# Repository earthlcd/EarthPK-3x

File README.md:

# EarthPK-3x Pico Pi Breakout Board for the 3x PCB

These are the design file for the EarthPK-3x Pico Pi Breakout Board that can be used with EarthLCD ezLCD-3x smart LCD's such asthe 3.5" ezLCD-303 and the ezLCD-304. Also this board with the mating DF-11 connector and the bare PCB along with a a bundled 4.3" ezLCD-3x is below: 

[ezLCD-3043-PK](https://earthlcd.com/products/ezlcd-3043-pk)

The arduino library to use the arduino IDE with this is below:

[arLCD Library](https://github.com/earthlcd/arLCDLib)

Schematic:
[REV-X2](https://github.com/earthlcd/EarthPK-3x/blob/master/schematics/ezLCD-303-PicoPi-Breakout-Board-REV-X2.pdf)

QuickStart Guide (coming soon)

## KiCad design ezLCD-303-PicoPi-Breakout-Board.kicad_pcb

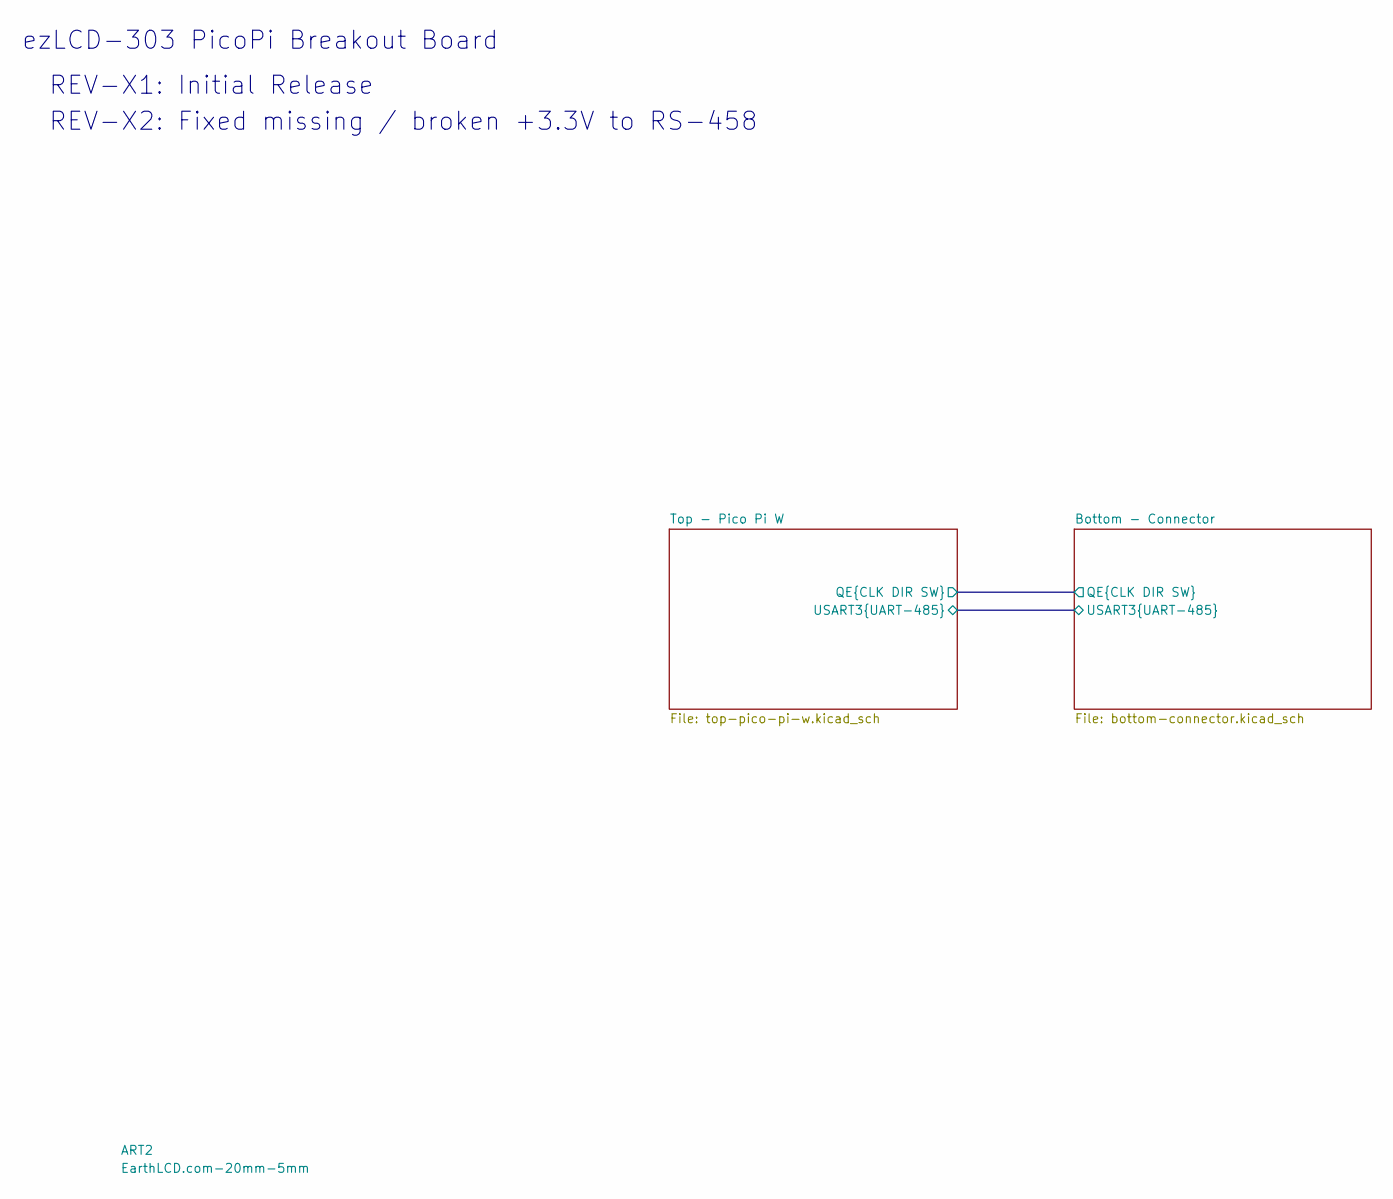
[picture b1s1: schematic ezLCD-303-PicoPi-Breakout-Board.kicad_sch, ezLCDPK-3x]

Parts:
ART2: EarthLCD.com-20mm-5mm; EarthLCD20mmX5mm

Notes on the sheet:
ezLCD-303 PicoPi Breakout Board
REV-X2: Fixed missing / broken +3.3V to RS-458
REV-X1: Initial Release

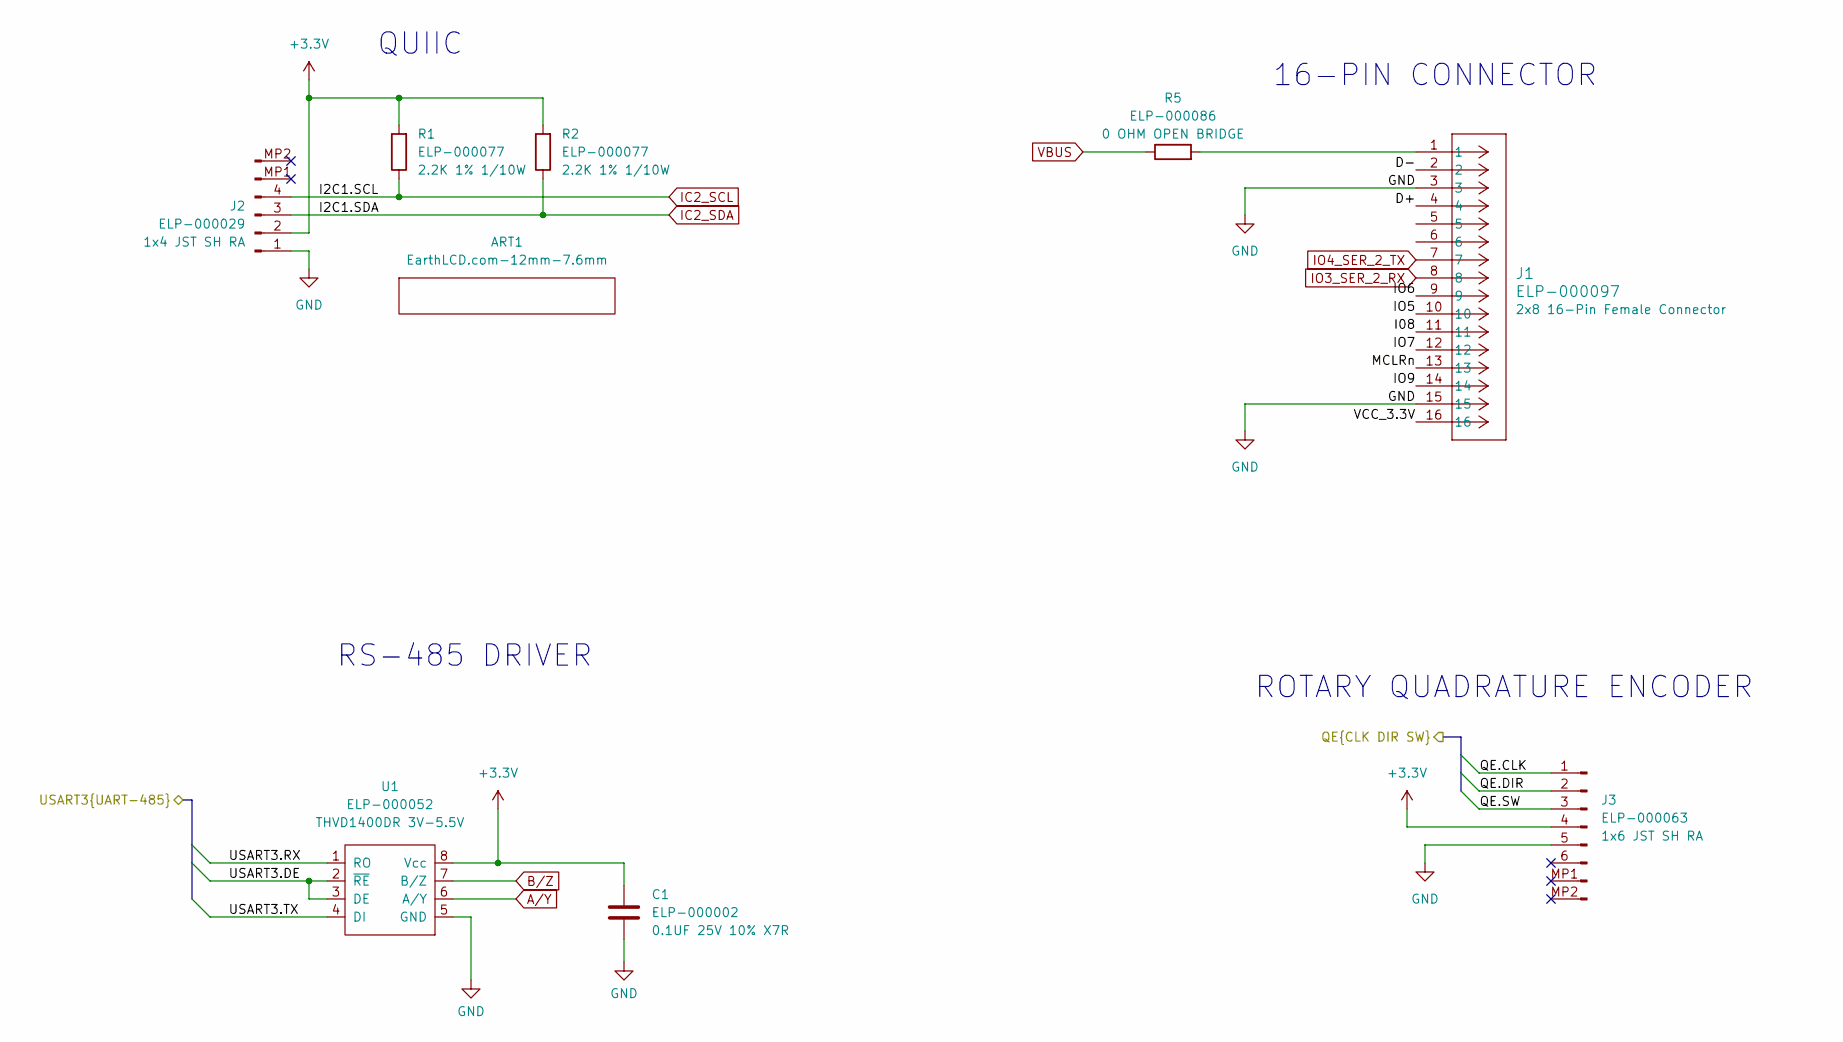
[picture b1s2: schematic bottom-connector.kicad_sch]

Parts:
ART1: EarthLCD.com-12mm-7.6mm; SparkFun-QWICC-Logo-4mm_x_1
C1: ELP-000002; C_0402_1005Metric
J1: ELP-000097
J2: ELP-000029; ELP-000029_JST_SH_SM04B-SRSS-TB_1x04-1MP_P1.00mm_Horizontal
J3: ELP-000063; ELP-000063_JST_SH_SM06B-SRSS-TB_1x06-1MP_P1.00mm_Horizontal
R1, R2: ELP-000077; R_0603_1608Metric
R5: ELP-000086
U1: ELP-000052; SO-8

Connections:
+3.3V: C1.1, J2.2, J3.4, R1.2, R2.2, U1.8 (Vcc); also elsewhere on the board
/Bottom - Connector/D+: J1.4
/Bottom - Connector/D-: J1.2
/Bottom - Connector/I08: J1.11
/Bottom - Connector/IO5: J1.10
/Bottom - Connector/IO6: J1.9
/Bottom - Connector/IO7: J1.12
/Bottom - Connector/IO9: J1.14
/Bottom - Connector/MCLRn: J1.13
/Bottom - Connector/QE.CLK: J3.1; also elsewhere on the board
/Bottom - Connector/QE.DIR: J3.2; also elsewhere on the board
/Bottom - Connector/QE.SW: J3.3; also elsewhere on the board
/Bottom - Connector/USART3.DE: U1.2 (~RE), U1.3 (DE)
/Bottom - Connector/USART3.RX: U1.1 (RO)
/Bottom - Connector/USART3.TX: U1.4 (DI)
/Bottom - Connector/VCC_3.3V: J1.16
A/Y: U1.6 (A/Y); also elsewhere on the board
B/Z: U1.7 (B/Z); also elsewhere on the board
GND: C1.2, J1.3, J1.15, J2.1, J3.5, U1.5 (GND); also elsewhere on the board
IC2_SCL: J2.4, R1.1; also elsewhere on the board
IC2_SDA: J2.3, R2.1; also elsewhere on the board
IO3_SER_2_RX: J1.8; also elsewhere on the board
IO4_SER_2_TX: J1.7; also elsewhere on the board
unnamed: J1.1, R5.2
VBUS: R5.1; also elsewhere on the board

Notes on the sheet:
RS-485 DRIVER
ROTARY QUADRATURE ENCODER
QUIIC
16-PIN CONNECTOR

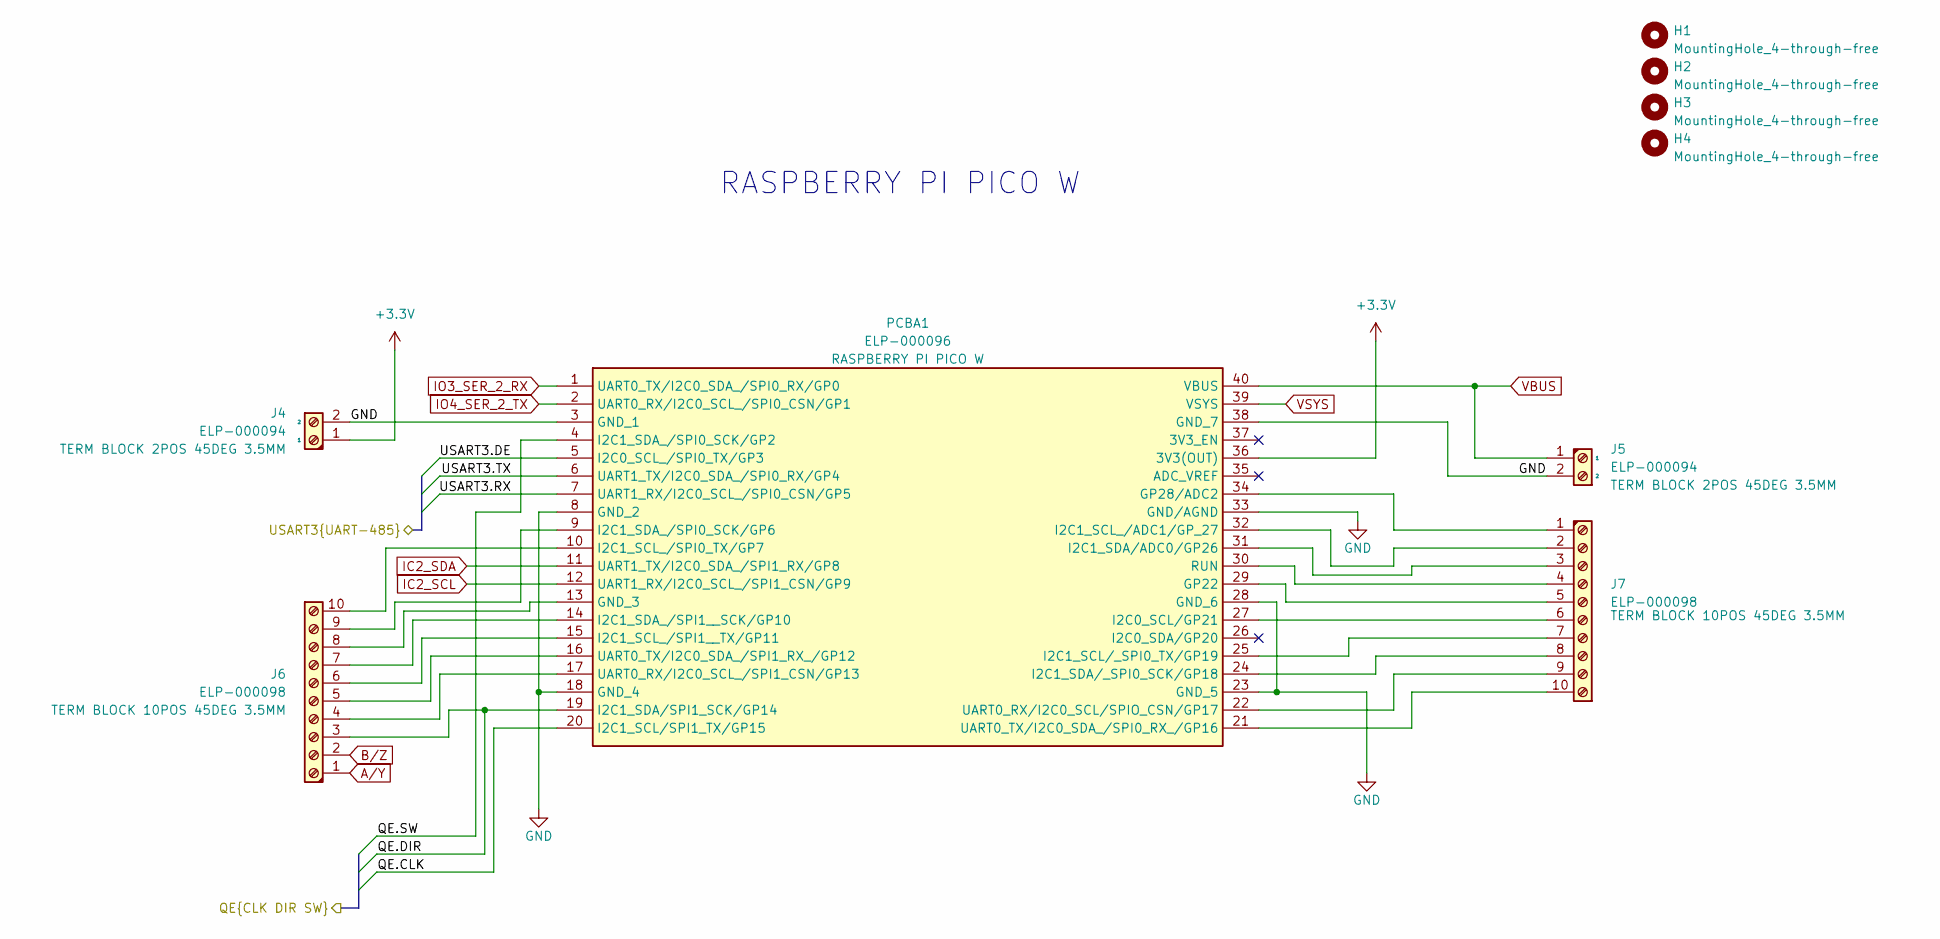
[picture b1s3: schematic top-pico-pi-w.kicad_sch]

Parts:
H1, H2, H3, H4: MountingHole_4-through-free
J4, J5: ELP-000094
J6, J7: ELP-000098
PCBA1: ELP-000096

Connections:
+3.3V: J4.1, PCBA1.36 (3V3(OUT)); also elsewhere on the board
/Bottom - Connector/QE.CLK: PCBA1.20 (I2C1_SCL/SPI1_TX/GP15); also elsewhere on the board
/Bottom - Connector/QE.DIR: J6.3, PCBA1.19 (I2C1_SDA/SPI1_SCK/GP14); also elsewhere on the board
/Bottom - Connector/QE.SW: PCBA1.4 (I2C1_SDA_/SPI0_SCK/GP2); also elsewhere on the board
/Top - Pico Pi W/USART3.DE: PCBA1.5 (I2C0_SCL_/SPI0_TX/GP3)
/Top - Pico Pi W/USART3.RX: PCBA1.7 (UART1_RX/I2C0_SCL_/SPI0_CSN/GP5)
/Top - Pico Pi W/USART3.TX: PCBA1.6 (UART1_TX/I2C0_SDA_/SPI0_RX/GP4)
A/Y: J6.1; also elsewhere on the board
B/Z: J6.2; also elsewhere on the board
GND: J4.2, J5.2, PCBA1.3 (GND_1), PCBA1.8 (GND_2), PCBA1.18 (GND_4), PCBA1.23 (GND_5), PCBA1.28 (GND_6), PCBA1.33 (GND/AGND), PCBA1.38 (GND_7); also elsewhere on the board
IC2_SCL: PCBA1.12 (UART1_RX/I2C0_SCL_/SPI1_CSN/GP9); also elsewhere on the board
IC2_SDA: PCBA1.11 (UART1_TX/I2C0_SDA_/SPI1_RX/GP8); also elsewhere on the board
IO3_SER_2_RX: PCBA1.1 (UART0_TX/I2C0_SDA_/SPI0_RX/GP0); also elsewhere on the board
IO4_SER_2_TX: PCBA1.2 (UART0_RX/I2C0_SCL_/SPI0_CSN/GP1); also elsewhere on the board
unnamed: J6.4, PCBA1.17 (UART0_RX/I2C0_SCL_/SPI1_CSN/GP13)
unnamed: J6.5, PCBA1.16 (UART0_TX/I2C0_SDA_/SPI1_RX_/GP12)
unnamed: J6.6, PCBA1.15 (I2C1_SCL_/SPI1__TX/GP11)
unnamed: J6.7, PCBA1.14 (I2C1_SDA_/SPI1__SCK/GP10)
unnamed: J6.8, PCBA1.13 (GND_3)
unnamed: J6.9, PCBA1.9 (I2C1_SDA_/SPI0_SCK/GP6)
unnamed: J6.10, PCBA1.10 (I2C1_SCL_/SPI0_TX/GP7)
unnamed: J7.1, PCBA1.34 (GP28/ADC2)
unnamed: J7.2, PCBA1.32 (I2C1_SCL_/ADC1/GP_27)
unnamed: J7.3, PCBA1.31 (I2C1_SDA/ADC0/GP26)
unnamed: J7.4, PCBA1.30 (RUN)
unnamed: J7.5, PCBA1.29 (GP22)
unnamed: J7.6, PCBA1.27 (I2C0_SCL/GP21)
unnamed: J7.7, PCBA1.25 (I2C1_SCL/_SPI0_TX/GP19)
unnamed: J7.8, PCBA1.24 (I2C1_SDA/_SPI0_SCK/GP18)
unnamed: J7.9, PCBA1.22 (UART0_RX/I2C0_SCL/SPIO_CSN/GP17)
unnamed: J7.10, PCBA1.21 (UART0_TX/I2C0_SDA_/SPI0_RX_/GP16)
VBUS: J5.1, PCBA1.40 (VBUS); also elsewhere on the board
VSYS: PCBA1.39 (VSYS)

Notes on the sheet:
RASPBERRY PI PICO W

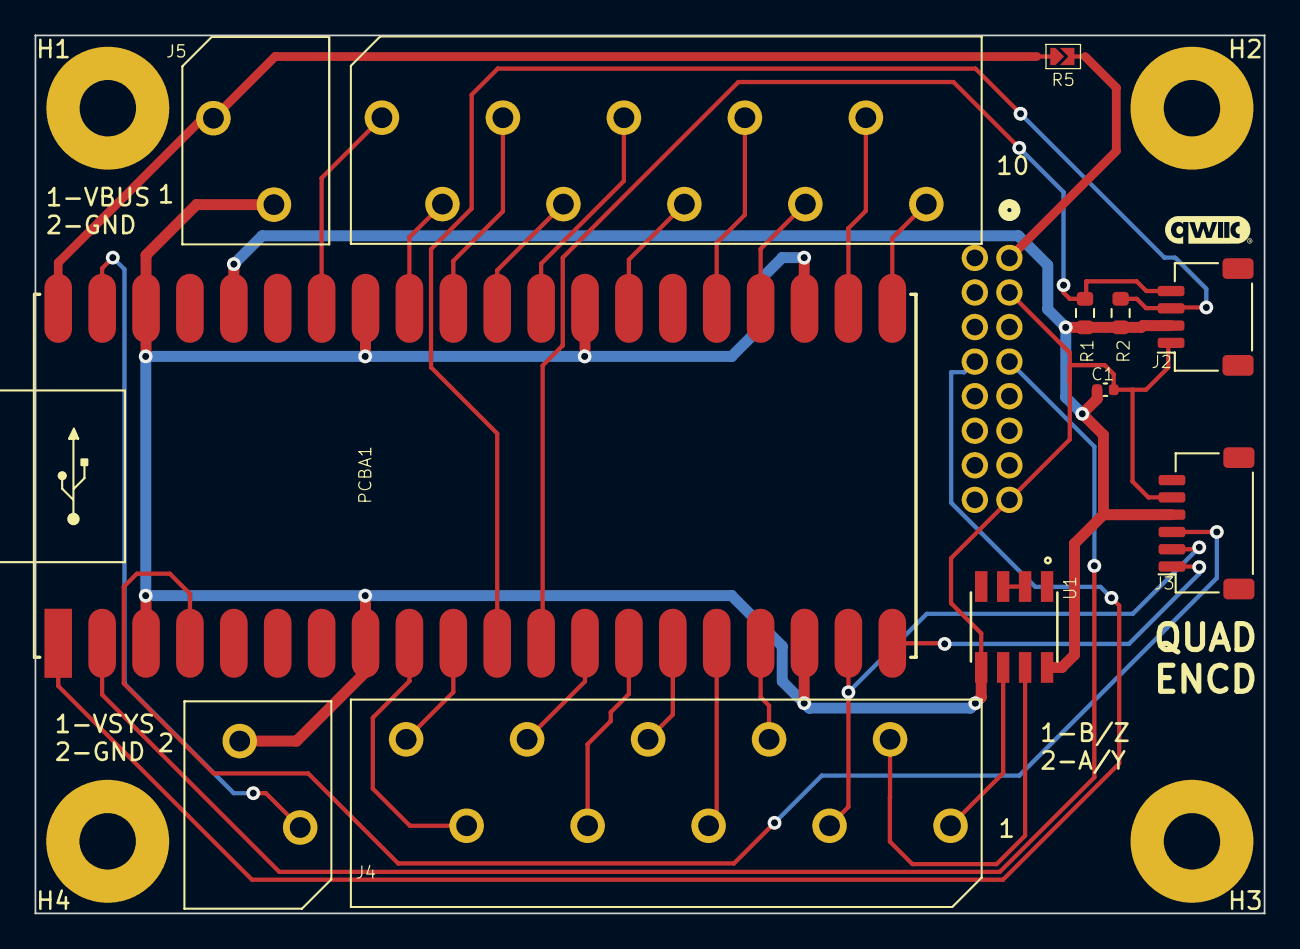
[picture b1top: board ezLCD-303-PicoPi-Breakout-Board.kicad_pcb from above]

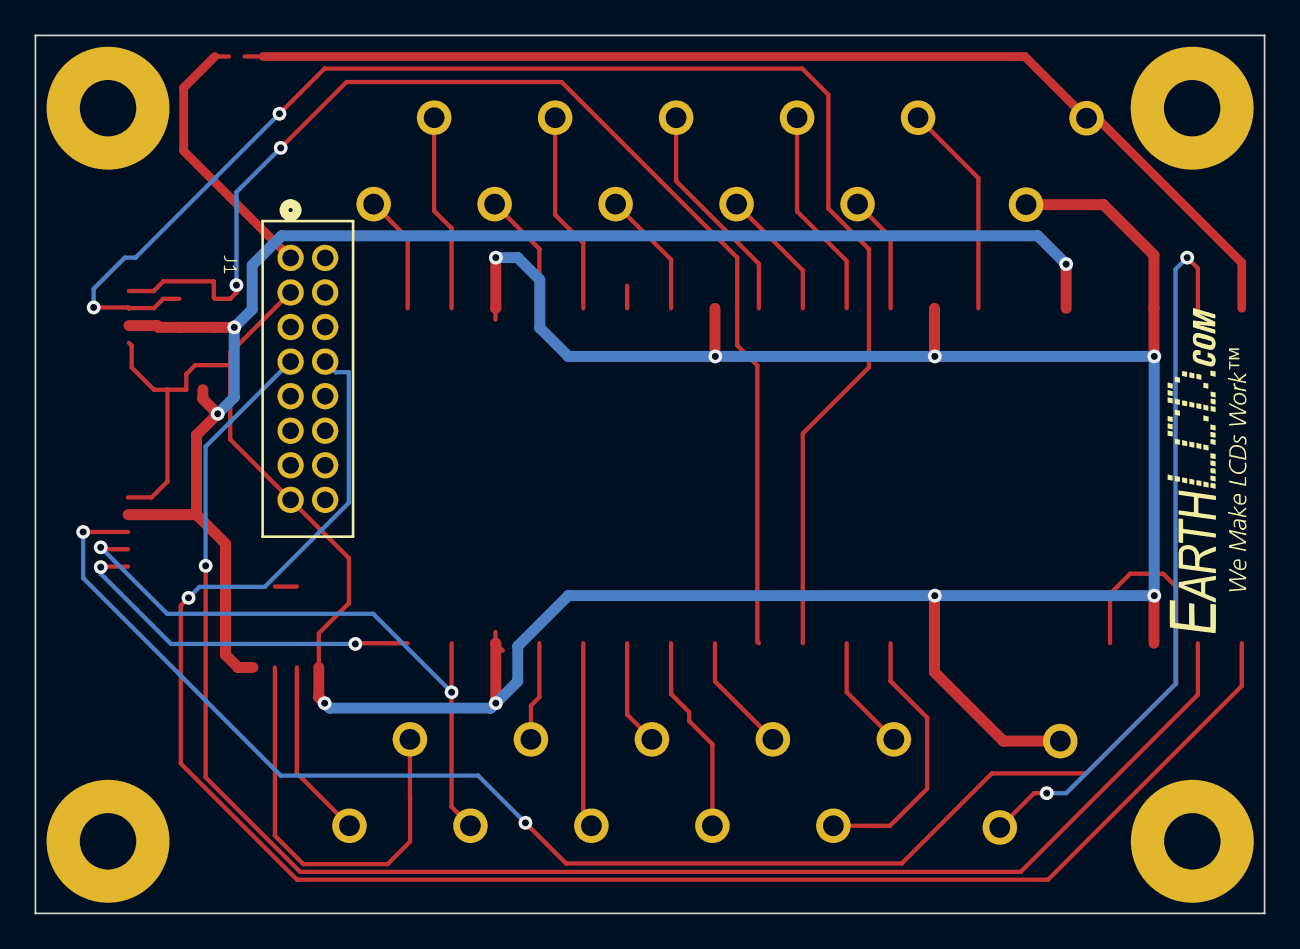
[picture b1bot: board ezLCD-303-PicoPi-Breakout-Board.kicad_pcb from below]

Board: 2 copper layers, 71.1 x 50.8 mm, 19 parts (2 on the bottom side), 31 nets.

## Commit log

2023-10-14 Initial commit.
2023-10-14 Adjusted origins on the PCB
2023-10-14 Added backup directory to repo.
2023-10-14 Added additional silk to help indicate connection points.
2023-10-14 After Generating Gerbers (X1)
2023-10-14 Added REV-X1 Gerbers
2023-10-14 Some how, the gerbers didn't get added to the zip.
2023-10-27 Fixed errors on the schematic found after fabrication of the X1 PCB's.
